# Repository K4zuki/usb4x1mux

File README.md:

# usb4x1mux
4x USB hosts multiplexed to one device

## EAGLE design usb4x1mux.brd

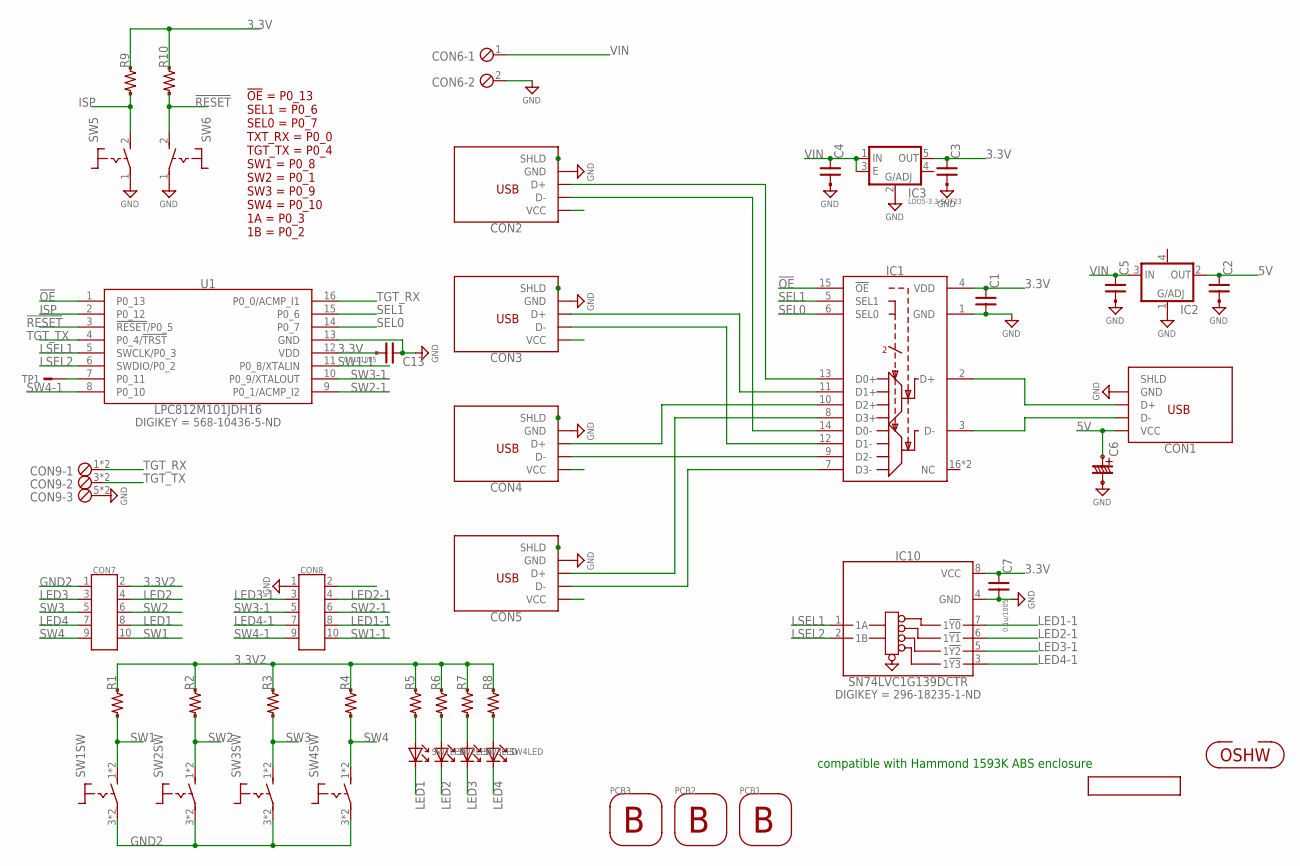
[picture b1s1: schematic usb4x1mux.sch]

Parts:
C1, C2, C3: C-SMD-0.1U-1608; CR-1608
C4, C5: C-SMD-10U-1608; CR-1608
C6: C-DENKAI-100U-875105142005WURTH; C-2.5PHI5-875105142005WURTH
C7, C13: 0.1u/1005; CR-1608
CON1: CON-USB-A-614104150121; CON-USB-614104150121WURTH
CON2, CON3, CON4, CON5: CON-USB-UB; CON-USB-47589-0001MOLEX
CON6: ETB43024B; ETB43024
CON7, CON8: CON-MIL-10-ARM3; PH127-2X5MG-1.5
CON9: CON-TANSHI3; CON-FFKV3
GIT1: GIT-REVISION_1.7
IC1: IC-USB-FSUSB74; QFN16-0.5P3.0X3.0
IC2: LDO4-5.0-SOT223; IC-SOT223
IC3: LDO5-3.3-SOT23; SOT95P280X145-5N
IC10: SN74LVC1G139DCTR; SOT65P315X290-8N
ICON1: ICON-OSHW
PCB1: HAMMOND-PCB-BK-1593K; HAMMOND-1593K
PCB2, PCB3: HAMMOND-PCB--66X28; HAMMOND-1593-28
R1, R2, R3, R4: R-US-10K-1608; R-1608-PADPAD
R5, R6, R7, R8, R9, R10: R-US-100R-1608; R-1608-PADPAD
SW1, SW2, SW3, SW4: TACTSW2-LED-WH-10SQ; TS-ALGWRH-G
SW5, SW6: TACTSW2-BK-AKI; SW-TACTSW-2P
TP1: TESTPAD; TP06RECT
U1: LPC812M101JDH16; SOT65P510X450X110-16N

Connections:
3.3V: C1.1, C3.1, C7.1, C13.2, CON8.2, IC1.4 (VDD), IC3.5 (OUT), IC10.8 (VCC), R9.1, R10.1, U1.12 (VDD)
3.3V2: CON7.2, R1.1, R2.1, R3.1, R4.1, R5.1, R6.1, R7.1, R8.1
5V: C2.1, C6.+, CON1.1 (VCC), IC2.2 (OUT)
!OE!: IC1.15 (!OE!), U1.1 (P0_13)
!RESET!: R10.2, SW6.2 (S), U1.3 (!RESET!/P0_5)
GND: C1.2, C2.2, C3.2, C4.2, C5.2, C6.-, C7.2, C13.1, CON1.4 (GND), CON2.5 (GND), CON3.5 (GND), CON4.5 (GND), CON5.5 (GND), CON6.2, CON8.1, CON9.5, CON9.6, IC1.1 (GND), IC2.1 (ADJ), IC3.2 (ADJ), IC10.4 (GND), SW5.1, SW6.1, U1.13 (GND)
GND2: CON7.1, SW1.3, SW1.4, SW2.3, SW2.4, SW3.3, SW3.4, SW4.3, SW4.4
ISP: R9.2, SW5.2 (S), U1.2 (P0_12)
LED1: CON7.8, SW1.- (K)
LED1-1: CON8.8, IC10.7 (1!Y0!)
LED2: CON7.4, SW2.- (K)
LED2-1: CON8.4, IC10.6 (1!Y1!)
LED3: CON7.3, SW3.- (K)
LED3-1: CON8.3, IC10.5 (1!Y2!)
LED4: CON7.7, SW4.- (K)
LED4-1: CON8.7, IC10.3 (1!Y3!)
LSEL1: IC10.1 (1A), U1.5 (SWCLK/P0_3)
LSEL2: IC10.2 (1B), U1.6 (SWDIO/P0_2)
unnamed: CON2.3 (D+), IC1.13 (D0+)
unnamed: CON2.2 (D-), IC1.14 (D0-)
unnamed: CON3.3 (D+), IC1.11 (D1+)
unnamed: CON3.2 (D-), IC1.12 (D1-)
unnamed: CON4.3 (D+), IC1.10 (D2+)
unnamed: CON4.2 (D-), IC1.9 (D2-)
unnamed: CON5.3 (D+), IC1.8 (D3+)
unnamed: CON5.2 (D-), IC1.7 (D3-)
unnamed: CON1.3 (D+), IC1.2 (D+)
unnamed: CON1.2 (D-), IC1.3 (D-)
unnamed: CON2.SHD (SHLD), CON2.SHD$1 (SHLD), CON2.SHD$2 (SHLD), CON2.SHD$3 (SHLD), CON2.SHD$4 (SHLD), CON2.SHD$5 (SHLD), CON2.SHD$6 (SHLD), CON2.SHD$7 (SHLD)
unnamed: CON3.SHD (SHLD), CON3.SHD$1 (SHLD), CON3.SHD$2 (SHLD), CON3.SHD$3 (SHLD), CON3.SHD$4 (SHLD), CON3.SHD$5 (SHLD), CON3.SHD$6 (SHLD), CON3.SHD$7 (SHLD)
unnamed: CON4.SHD (SHLD), CON4.SHD$1 (SHLD), CON4.SHD$2 (SHLD), CON4.SHD$3 (SHLD), CON4.SHD$4 (SHLD), CON4.SHD$5 (SHLD), CON4.SHD$6 (SHLD), CON4.SHD$7 (SHLD)
unnamed: CON5.SHD (SHLD), CON5.SHD$1 (SHLD), CON5.SHD$2 (SHLD), CON5.SHD$3 (SHLD), CON5.SHD$4 (SHLD), CON5.SHD$5 (SHLD), CON5.SHD$6 (SHLD), CON5.SHD$7 (SHLD)
unnamed: R5.2, SW1.+ (A)
unnamed: R6.2, SW2.+ (A)
unnamed: R7.2, SW3.+ (A)
unnamed: R8.2, SW4.+ (A)
unnamed: TP1.TP, U1.7 (P0_11)
SEL0: IC1.6 (SEL0), U1.14 (P0_7)
SEL1: IC1.5 (SEL1), U1.15 (P0_6)
SW1: CON7.10, R1.2, SW1.1 (S), SW1.2 (S)
SW1-1: CON8.10, U1.11 (P0_8/XTALIN)
SW2: CON7.6, R2.2, SW2.1 (S), SW2.2 (S)
SW2-1: CON8.6, U1.9 (P0_1/ACMP_I2)
SW3: CON7.5, R3.2, SW3.1 (S), SW3.2 (S)
SW3-1: CON8.5, U1.10 (P0_9/XTALOUT)
SW4: CON7.9, R4.2, SW4.1 (S), SW4.2 (S)
SW4-1: CON8.9, U1.8 (P0_10)
TGT_RX: CON9.1, CON9.2, U1.16 (P0_0/ACMP_I1)
TGT_TX: CON9.3, CON9.4, U1.4 (P0_4/!TRST!)
VIN: C4.1, C5.1, CON6.1, IC2.3 (IN), IC3.1 (IN), IC3.3 (E)

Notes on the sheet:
!OE! = P0_13 SEL1 = P0_6 SEL0 = P0_7 TXT_RX = P0_0 TGT_TX = P0_4 SW1 = P0_8 SW2 = P0_1 SW3 = P0_9 SW4 = P0_10 1A = P0_3 1B = P0_2
compatible with Hammond 1593K ABS enclosure

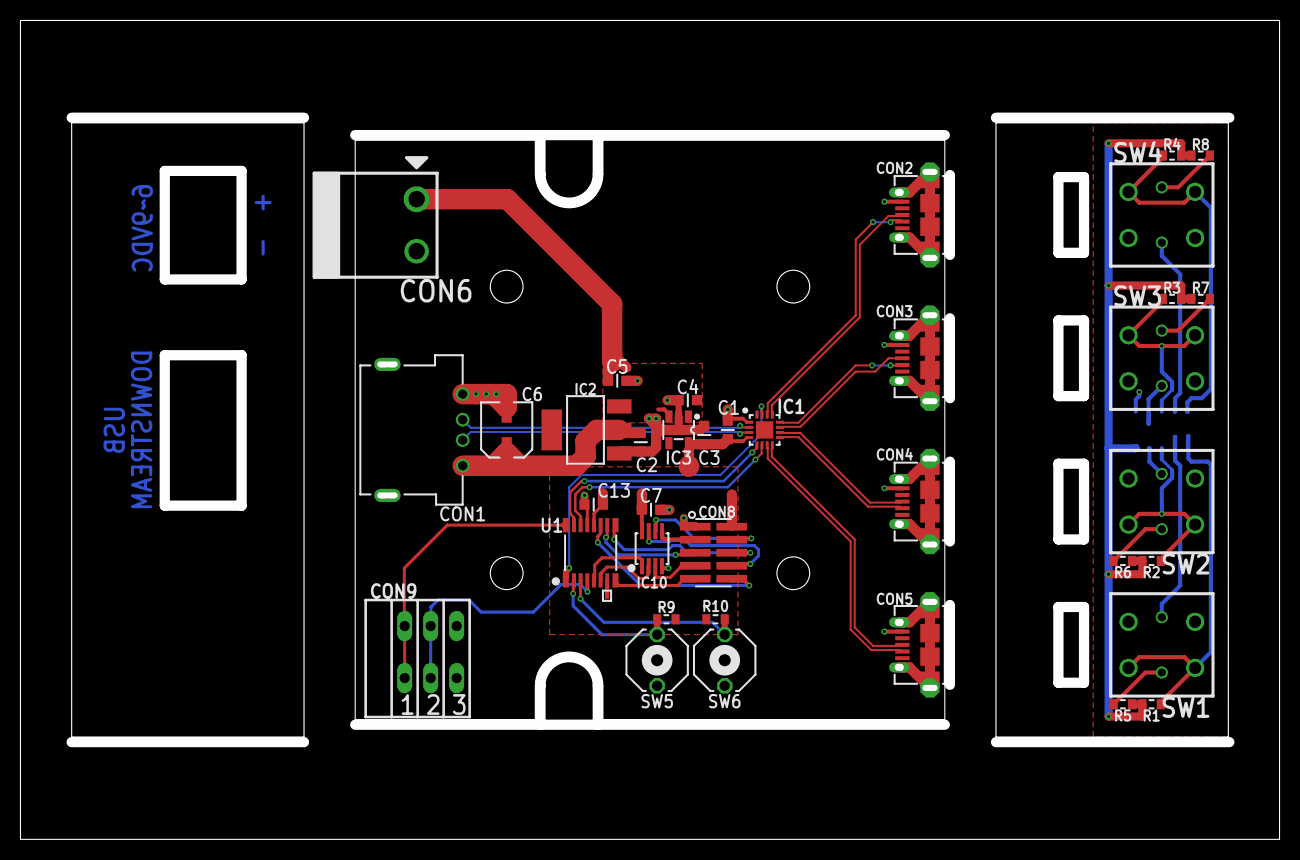
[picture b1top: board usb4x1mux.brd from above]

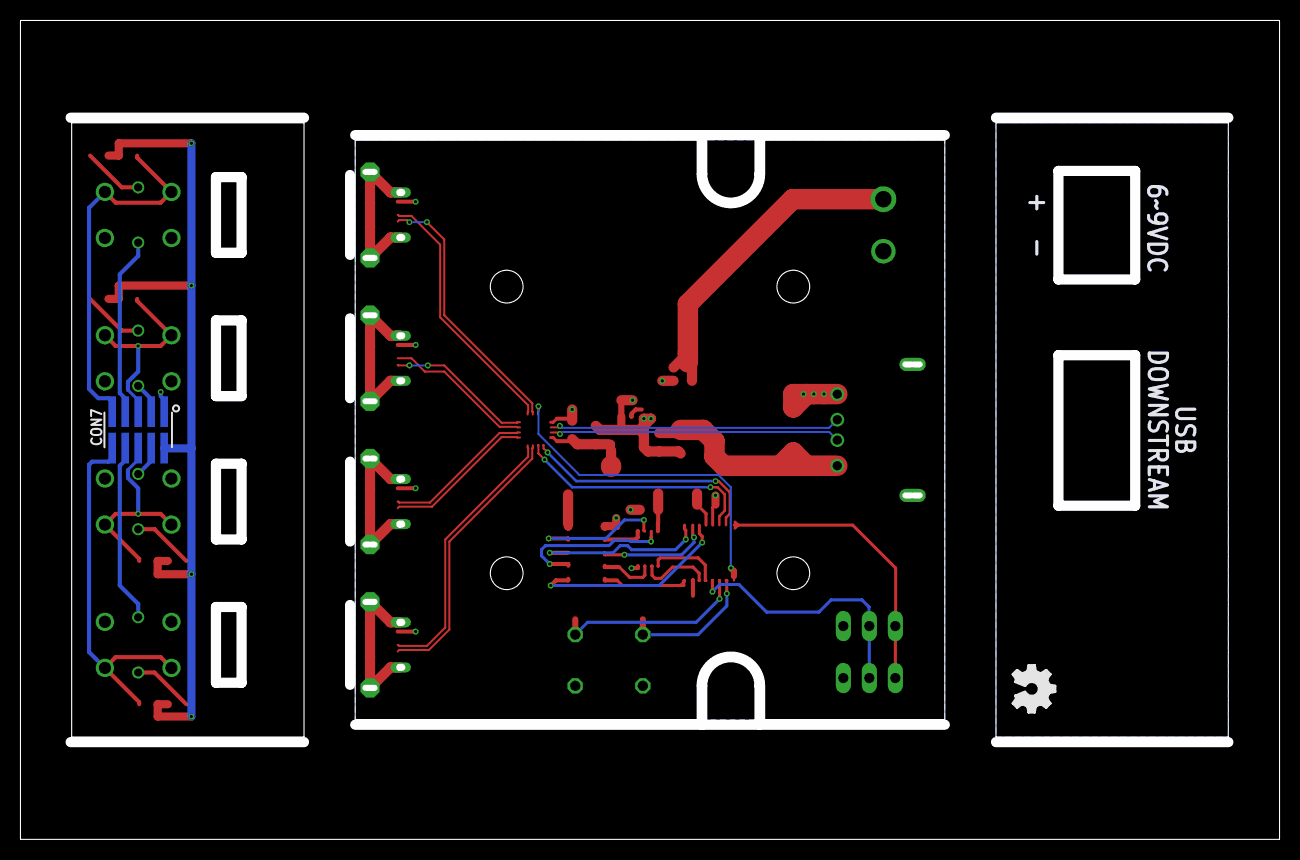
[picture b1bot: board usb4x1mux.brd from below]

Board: 2 copper layers, 122.0 x 79.0 mm, 44 parts (2 on the bottom side), 50 nets.

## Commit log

2018-01-01 prepare circleci builds
2018-01-01 add sch and brd
2018-01-01 update panel width
2018-01-01 add gerber files
2018-01-01 update schematic
2018-01-01 update gerber files
2018-01-01 update panel layout
2018-01-01 apply updates to gerbers
2018-01-01 move git tag mark
2018-01-01 update library; move git hash tag silk
2018-01-01 update library
2018-01-01 update hosts panel layout
    it was keepout violation
2018-01-01 apply layout update to gerbers
2018-01-01 update CI config
2018-01-01 update compatible enclosure list
2018-12-09 update CI config [ci skip]
